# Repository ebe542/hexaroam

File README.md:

# HexaRoam

A modular six-legged robot built to explore — a learning project in Rust, robotics, and AI.

## Status

Rust firmware for Raspberry Pi Pico (RP2040) generates synchronous two-channel servo signals through one PIO state machine and DMA. Separate hardware tests exercise signal-plan switching, persistent faults, explicit restart after underflow, and aborting active DMA before recovery. The normal demo includes buffered UART logging and bounded panic output. The owner reported 169 passing unit tests and successful manual logging, panic, and recovery checks. The transactional angle-command bank and signal-plan adapter are host-tested and have passed a combined Pico angle-command signal check. A separate hardware test also verifies an exhausted DMA-abort budget and subsequent recovery. The normal firmware remains a fixed-plan demo; attached-servo operation and autonomous behavior are not yet verified. See the [firmware guide](firmware/README.md) for the verification record.

## Goals

- Build servo control, communication, kinematics, gait generation, and behavior logic step by step.
- Start with one general-purpose Raspberry Pi Pico and Rust.
- Add Pico output expansion modules when needed.
- Adapt the mechanical reference design and document each built configuration.
- Develop autonomous exploration, interaction, and later custom AI models.
- Keep ROS integration optional.

## Repository layout

| Directory | Contents |
| --- | --- |
| docs/ | Architecture, milestones, and decisions |
| hardware/mechanics/ | CAD, print files, and assembly |
| hardware/electronics/ | Wiring, power distribution, and board connections |
| hardware/bom/ | Bills of materials |
| hardware/references/ | Versioned official datasheets and reference documents |
| firmware/ | Rust firmware for Pico controllers |
| software/ | Motion, sensors, navigation, and behavior |
| simulation/ | Robot models and simulation experiments |
| tools/ | Calibration and diagnostics |
| configs/ | Geometry, joint mapping, and calibration |

Start with the [visual architecture maps](docs/architecture/README.md), [project architecture](docs/architecture.md) and [milestones](docs/milestones.md).

## Hardware reference

The initial mechanical reference is [ggldnl/Hexapod-Hardware](https://github.com/ggldnl/Hexapod-Hardware), published under CERN-OHL-W-2.0. Upstream CAD and code are not bundled in this scaffold. Record provenance and applicable licenses when importing files; see [hardware attribution](hardware/ATTRIBUTION.md).

Official Pico and RP2040 PDFs, versions, licenses, and checksums are listed in [hardware references](hardware/references/README.md).

## Development

Rust is planned for firmware, communication, kinematics, and motion control. Python is planned for AI training, analysis, and experiments. The selected board is the existing Raspberry Pi Pico with RP2040, using the Rust target `thumbv6m-none-eabi`. Rust, rust-analyzer, and the embedded target are installed on the Windows development host. The blink and adjustable PIO pulse firmware has been built and run on the Pico. The communication bus and later Linux host environment remain open.

Follow the [development setup guide](docs/development-setup.md) for Windows with Git Bash or Ubuntu. It separates confirmed setup results from pending verification.

See the [firmware guide](firmware/README.md) for build, UF2 conversion, USB transfer, and the manual verification record. Ubuntu setup is documented but has not been verified for this project.

## Licensing

Original HexaRoam software and documentation are licensed under the [MIT License](LICENSE). Third-party materials, including imported or derived hardware designs, retain their applicable licenses; see [hardware attribution](hardware/ATTRIBUTION.md).

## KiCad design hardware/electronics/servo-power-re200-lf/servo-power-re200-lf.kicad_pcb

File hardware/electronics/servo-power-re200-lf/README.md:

# One-servo protected supply on Roth RE200-LF

Revision P1, 2026-10-27. **UNBUILT placement and hand-wiring proposal.** The schematic remains [revision C](../pico-servo-system/README.md); electrical calculations and commissioning limits are in [discrete-shunt-design.md](../pico-servo-system/discrete-shunt-design.md). This layout does not establish successful protection or a current rating.

## Files and physical scope

- [Editable KiCad board](servo-power-re200-lf.kicad_pcb) and [project](servo-power-re200-lf.kicad_pro).
- [Four-page assembly guide](assembly-guide.pdf): 1 component view, 2 mirrored solder view, 3 load wiring, 4 control wiring. A4 landscape, actual size; verify the 50-mm calibration bar and real hole alignment before use.
- [Pin map](pin-map.csv), [wire list](wiring.csv), [assembly BOM](assembly-bom.csv), [layout model](layout-model.json), [check record](layout-check.json).
- SVG views provide the same geometry with hover labels. Hole IDs always refer to the component view: C01..C61, R01..R38. Solder views mirror columns horizontally only.

26 schematic components correspond to 54 physical pins, plus four existing-pad wire junctions BV/BG/BD/GS. The board has 30 footprints, 58 occupied holes and 47 insulated wire connections. U202 pin7 is intentionally unconnected. No copper tracks are provided; KiCad unrouted indications are expected. Do not export Gerbers for fabrication. Native front-side THT rings are virtual; the actual RE200-LF is single-sided, unplated, with underside pads only.

SW201 and R208 footprints represent **two-pole cable interfaces**, not the physical switch and resistor. Install the actual APEM switch separately on its bracket and the actual ARCOL HS25 2.2-ohm resistor on a suitable external heatsink. Never replace either external component with a wire short. If the optional switch is deliberately omitted, bypass its interface only with a suitably rated conductor. Keep the dump loop short and supported; the layout reserves board space, not a thermal enclosure design.

This supply is for **one servo only**. The Pico baseboard has its own Manson-to-VSYS feed; it is not powered from J202. Connect shared signal ground according to the system schematic. Three output modules reserve eighteen servo signals, but the present supply is not an eighteen-servo distribution board.

## Parts and fit

Use [the BOM](assembly-bom.csv) together with [mechanical part references](../pico-servo-system/power-layout-components.md). Four Phoenix 1715721 / MKDS 1.5/2-5.08 terminals are proposed for J201, J202 and the SW201/R208 interfaces. Equivalent terminals require their own body, drill, pin and current-rating check.

- C201, owner measured: 1000 uF/25 V, diameter 10 mm, height 20 mm, approximately 5-mm wire spacing. Gently form to 5.08 mm without stressing the seal. Pin1 positive, pin2 negative. C202/C203 are provisional 100-nF disc envelopes; match actual parts before soldering.
- F201 holder: ESKA 503.400, cover 503.310, fuse 5x20 mm. Body 22x9x13.5 mm. Native pitch 22.60 mm versus nine grid intervals = 22.86 mm. Form terminal ends gently by about 0.13 mm per side when centered; do not force the holder. Dry fit before populating. T2.5A remains a provisional fuse choice pending measured behavior.
- Widen only the occupied terminal/Q201 holes to 1.3 mm, F201/D201/D202 holes to 1.5 mm; see pin-map.csv. Existing pad diameter remains 2.2 mm (nominal annulus 0.35 mm at 1.5-mm drill). Inspect for pad damage and support heavy parts/wires mechanically. Drilling/fit is not physically verified.
- U201 is specifically ST TL431CZ: REF1, anode2, cathode3. The wide TO-92 row requires spreading leads to 2.54-mm spacing. Do not substitute another TL431 package/pinout without checking its datasheet.
- U202 is LM393 in DIP8, notch toward the upper board edge. Verify pin1 before insertion. Q201 is IRLZ44NPBF: gate1, drain2, source3. Its metal tab is drain; insulate mounting hardware/heatsink as required. Other package variants require review.
- D201 SR540 and D202 1N5822: stripe/cathode = pin1, anode = pin2. The DO-201AD envelopes and 15.24-mm formed spacing are proposed; verify actual diameters and leads.
- R201..R207 use 10.16-mm axial spacing and a 6.3x2.5-mm body envelope; select ratings from the circuit design. R208 is external and is not an axial board resistor.
- Optional M1..M4 mounting reserves are drawn, not factory holes. Check actual mounting clearances before drilling. Leave room above the 20-mm capacitor, fuse cover and screw terminals.

Local capacitor/holder footprints are derived from KiCad standard geometry or explicit manufacturer dimensions. The capacitor lead spacing and fuse terminal spacing adaptations are documented; library licensing follows the KiCad Libraries License with its electronic-design exception. The two-pin holder geometry is original project material.

## Connections and assembly order

1. Print at actual size, check the ruler, board orientation and parts against their envelopes. Dry fit the fuse holder, terminals, capacitors and MOSFET before drilling or soldering.
2. Fit low components, DIP socket if used, then taller components. Keep fuse removed, both supplies disconnected and external cables disconnected during continuity work.
3. Install the load wires from PDF page3 / CSV group `load`. Use insulated conductors sized for the measured load and dump currents, reinforced at pad nodes. A drawn line indicates endpoints, not a bare solder bridge. Do not rely on 35-um isolated pad copper or a small component lead as a power bus. BV/BG/BD are junction pads only, not extra purchased parts.
4. Install control wires from page4 / group `control`. GS provides quiet ground; join it at Q201 source as listed. R207 returns directly to that source. Keep reference/sense wiring away from dump-current wiring. Crossings are insulated passovers, never implicit junctions.
5. Connect external switch/resistor harnesses. SW201 terminal1 is fused input, terminal2 goes to D201 anode. R208 terminal1 is SERVO_VS, terminal2 is MOSFET drain. The resistor has no polarity. Check actual switch ON contact pair before attachment.
6. Inspect diode/capacitor polarity, transistor/reference pinout, resistance between rails and every listed endpoint with power off. Do not treat the check record as a substitute for these measurements.
7. Follow the existing staged [commissioning plan](../pico-servo-system/discrete-shunt-design.md) before attaching a servo. Normal rail target is 5.0-5.3 V. The dump nominal thresholds are not guaranteed maximum transient voltages. Startup, PSU interaction, clamp behavior, fuse selection and heating remain unverified.

J201: pin1 PSU positive, pin2 ground. J202: pin1 SERVO_VS, pin2 ground. Test points: TP201 rail, TP202 ground, TP203 reference, TP204 sense, TP205 gate, TP206 drain. Support cables so screw-terminal forces cannot peel pads. The external resistor may dissipate substantial power; its nameplate rating assumes appropriate cooling.

## Review boundaries

The exported board is checked against a fresh revision-C netlist: references, values, nets, pad positions, drill sizes, body envelopes, distinct occupied holes, wire-graph completeness, polarities and quiet-ground topology. These are artifact checks, not hardware tests. Wire routes are endpoint guides; actual routing, clearances, joints, transient response and thermal behavior require manual review and bench measurements. No firmware changes or firmware tests were made.

All layout files are a consistent snapshot. Moving a footprint in KiCad does not update the CSV/PDF/SVG/model automatically. Update and recheck every artifact before assembly. Do not update this board from the whole three-sheet schematic without explicitly filtering the supply sheet: the other sheets belong to separate physical boards.

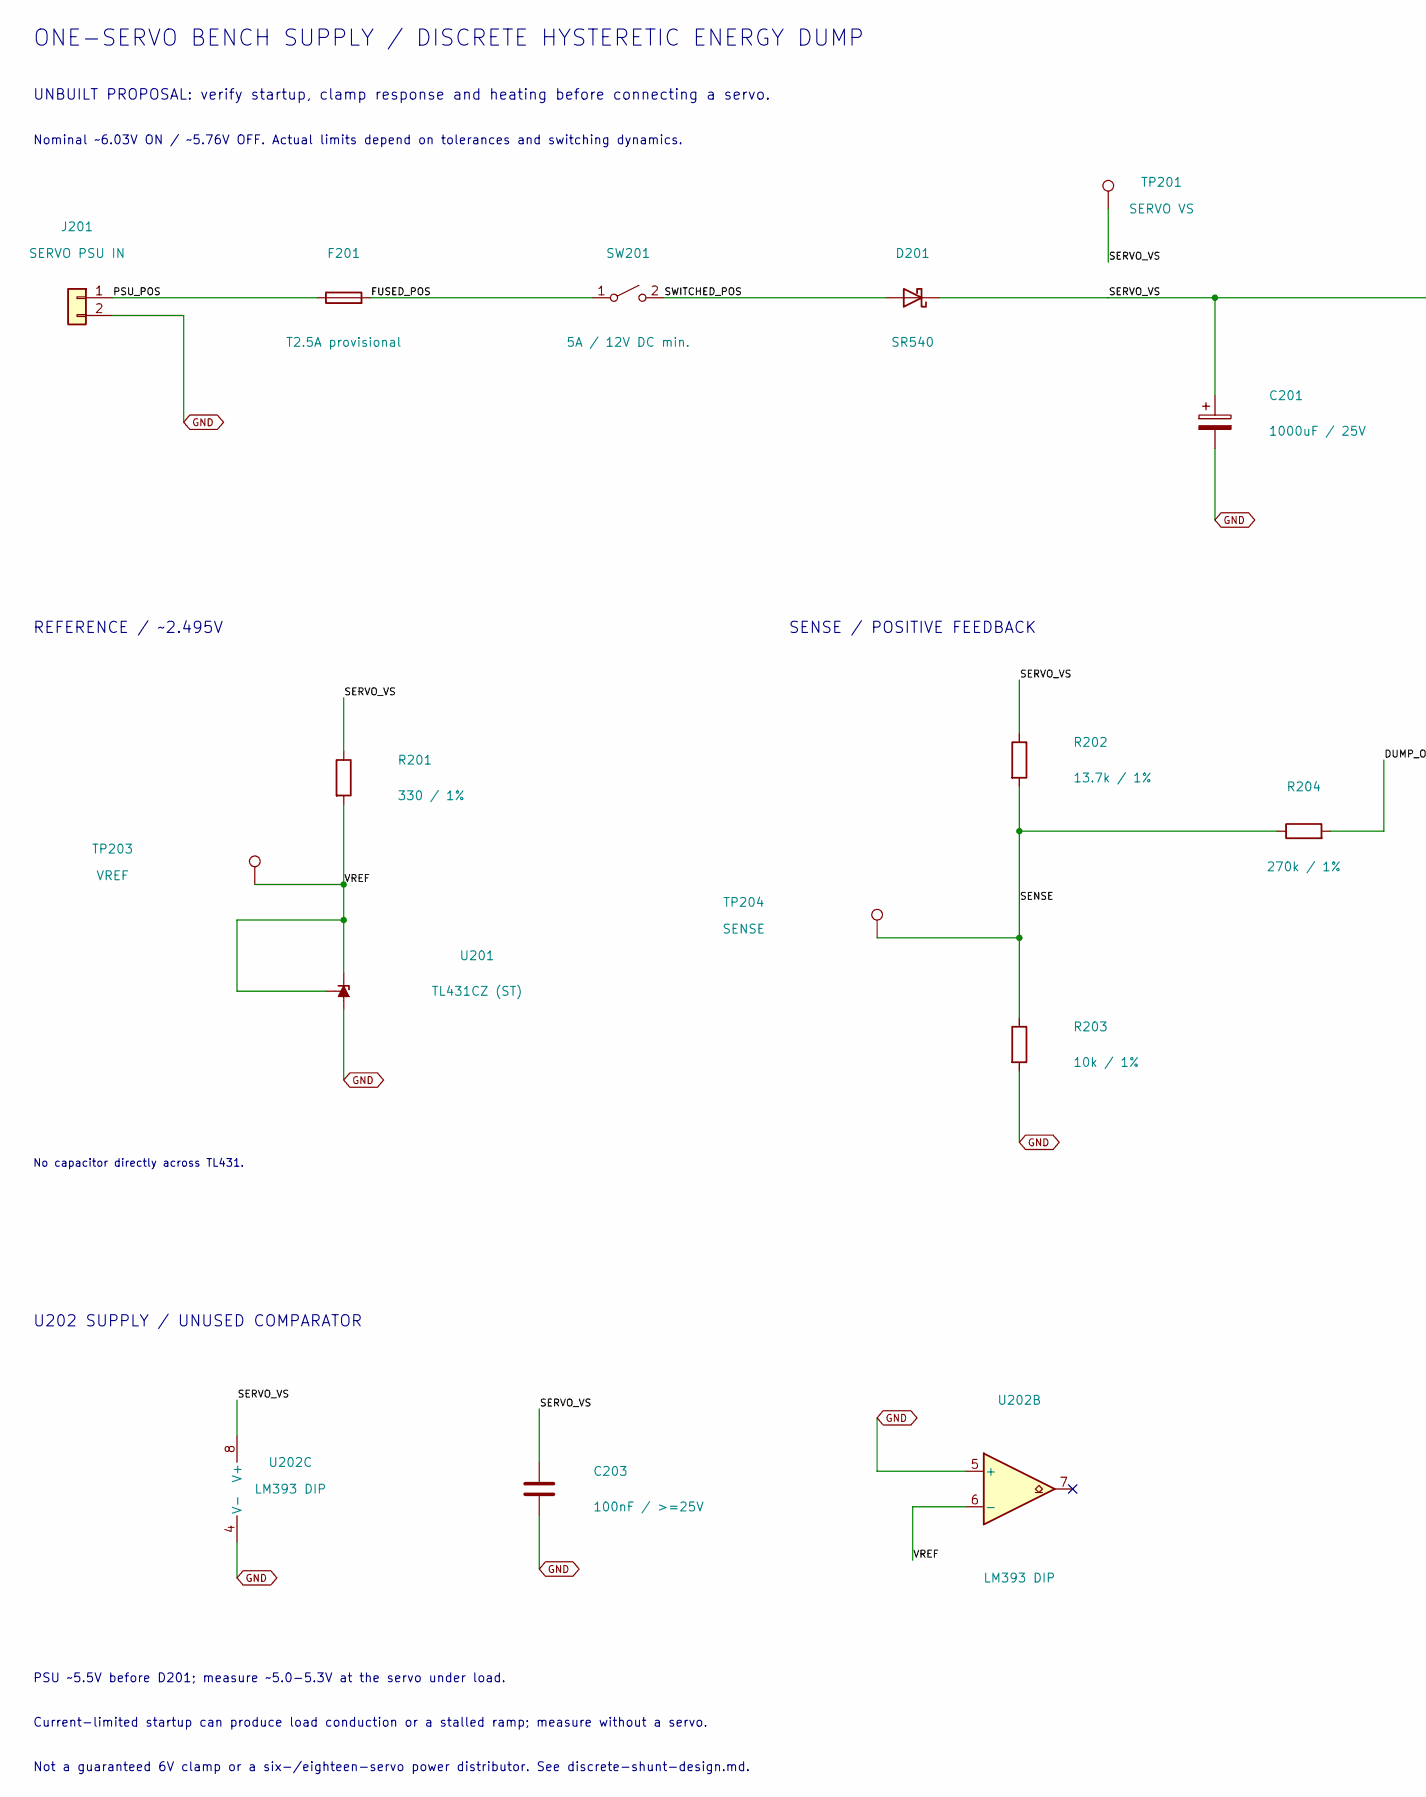
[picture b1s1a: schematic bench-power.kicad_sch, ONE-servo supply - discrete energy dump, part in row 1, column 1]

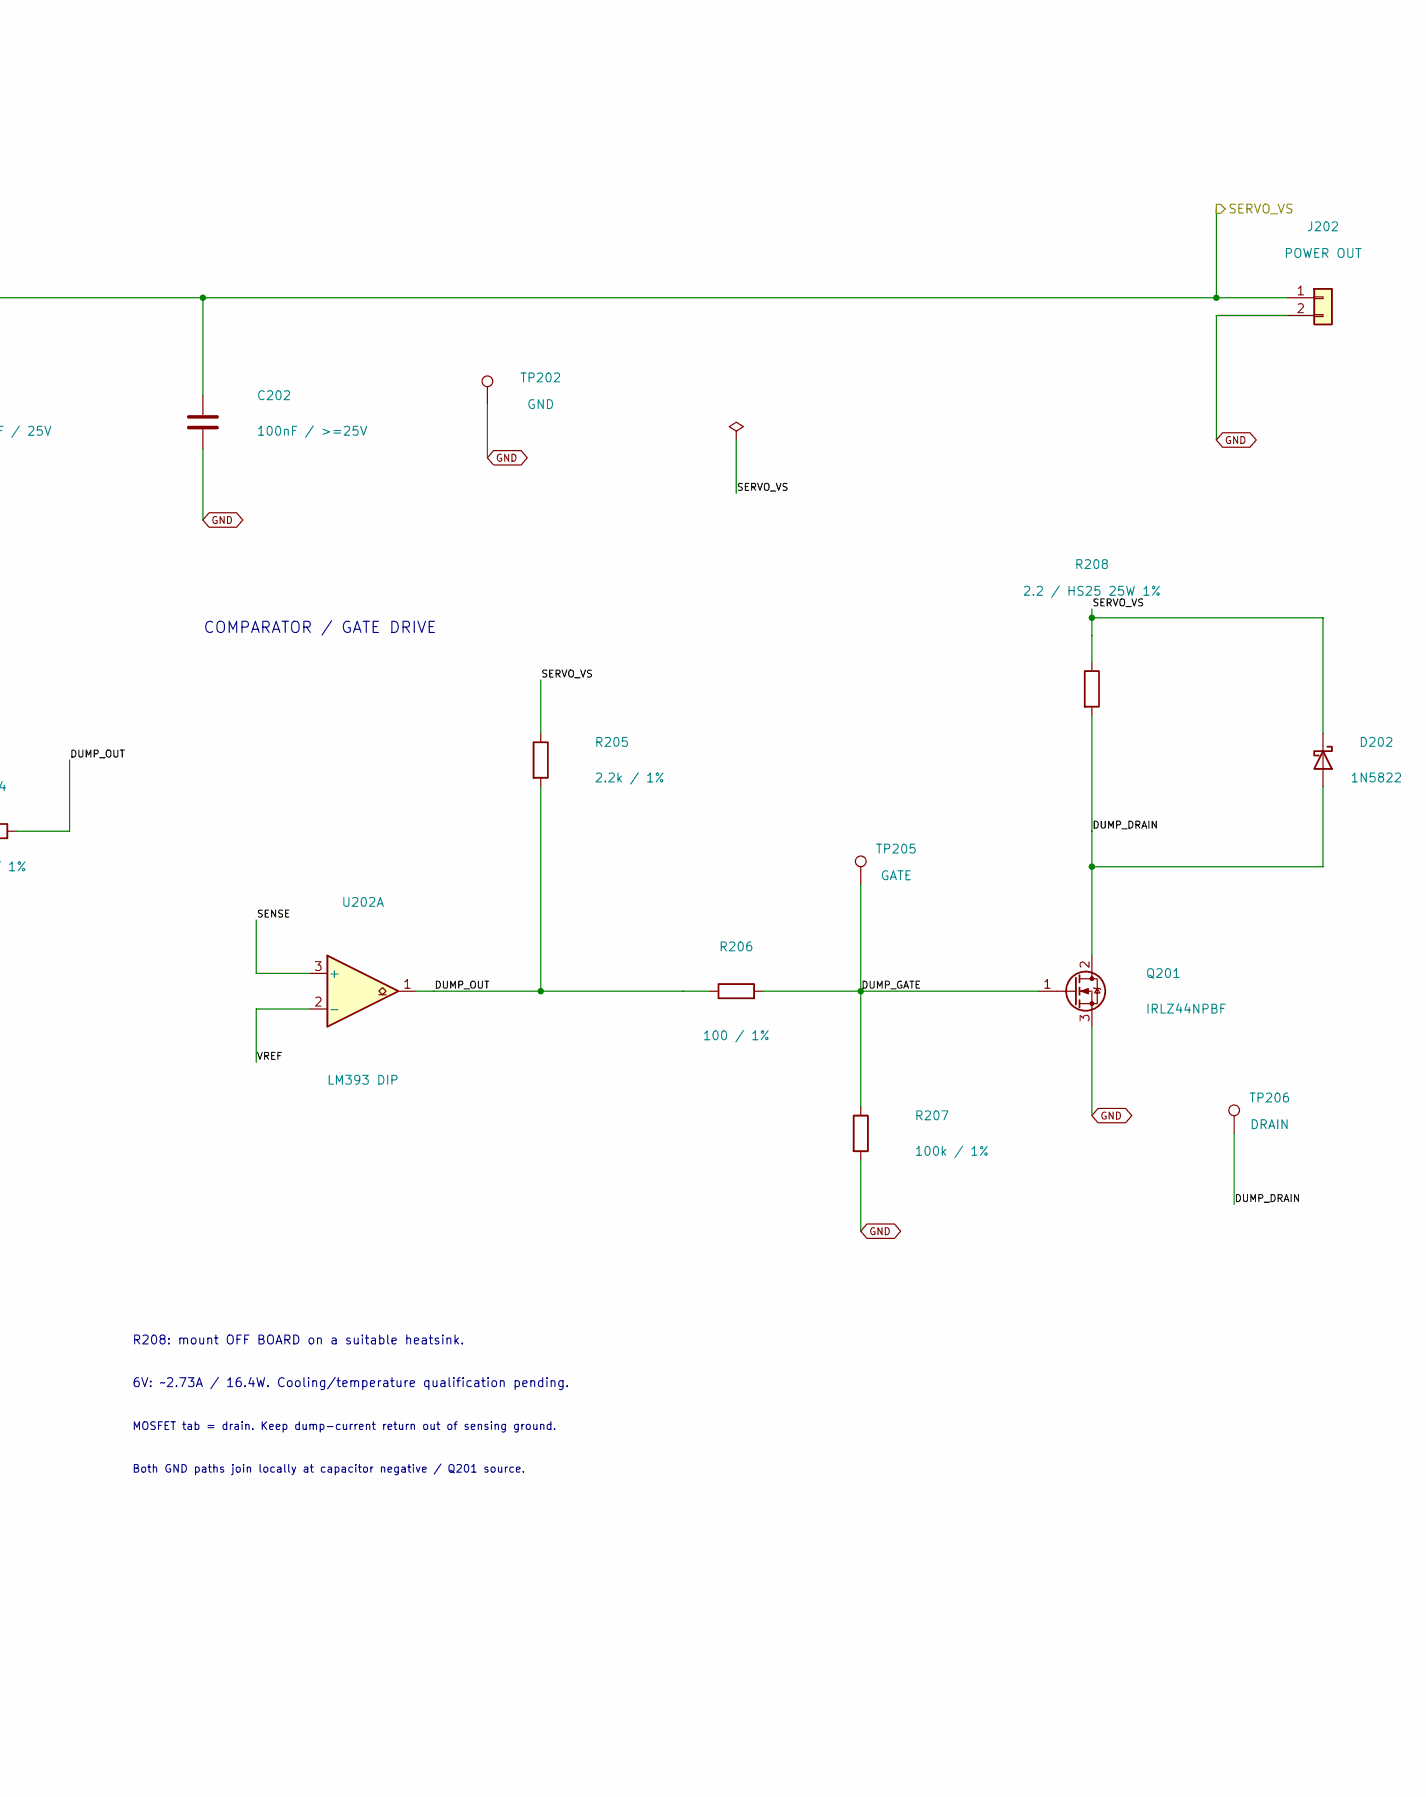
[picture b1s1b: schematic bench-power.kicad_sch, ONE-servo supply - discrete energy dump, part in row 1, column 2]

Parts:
C201: 1000uF / 25V
C202, C203: 100nF / >=25V
D201: SR540
D202: 1N5822
F201: T2.5A provisional
J201: SERVO PSU IN
J202: POWER OUT
Q201: IRLZ44NPBF; TO-220-3_Vertical
R201: 330 / 1%
R202: 13.7k / 1%
R203: 10k / 1%
R204: 270k / 1%
R205: 2.2k / 1%
R206: 100 / 1%
R207: 100k / 1%
R208: 2.2 / HS25 25W 1%
SW201: 5A / 12V DC min.
TP201: SERVO VS
TP202: GND
TP203: VREF
TP204: SENSE
TP205: GATE
TP206: DRAIN
U201: TL431CZ (ST); TO-92_Inline
U202: LM393 DIP; DIP-8_W7.62mm

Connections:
/ONE-SERVO protected supply/DUMP_DRAIN: D202.2 (A), Q201.2 (D), R208.2, TP206.1; also elsewhere on the board
/ONE-SERVO protected supply/DUMP_GATE: Q201.1 (G), R206.2, R207.1, TP205.1
/ONE-SERVO protected supply/DUMP_OUT: R204.2, R205.2, R206.1, U202.1
/ONE-SERVO protected supply/FUSED_POS: F201.2, SW201.1 (A)
/ONE-SERVO protected supply/PSU_POS: F201.1, J201.1
/ONE-SERVO protected supply/SENSE: R202.2, R203.1, R204.1, TP204.1, U202.3 (+)
/ONE-SERVO protected supply/SWITCHED_POS: D201.2 (A), SW201.2 (B)
/ONE-SERVO protected supply/VREF: R201.2, TP203.1, U201.1 (REF), U201.3 (K), U202.2 (-), U202.6 (-)
/SERVO_VS: C201.1, C202.1, C203.1, D201.1 (K), D202.1 (K), J202.1, R201.1, R202.1, R205.1, R208.1, TP201.1, U202.8 (V+); also elsewhere on the board
GND: C201.2, C202.2, C203.2, J201.2, J202.2, Q201.3 (S), R203.2, R207.2, TP202.1, U201.2 (A), U202.4 (V-), U202.5 (+); also elsewhere on the board

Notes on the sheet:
ONE-SERVO BENCH SUPPLY / DISCRETE HYSTERETIC ENERGY DUMP
UNBUILT PROPOSAL: verify startup, clamp response and heating before connecting a servo.
Nominal ~6.03V ON / ~5.76V OFF. Actual limits depend on tolerances and switching dynamics.
REFERENCE / ~2.495V
No capacitor directly across TL431.
SENSE / POSITIVE FEEDBACK
COMPARATOR / GATE DRIVE
U202 SUPPLY / UNUSED COMPARATOR
R208: mount OFF BOARD on a suitable heatsink.
6V: ~2.73A / 16.4W. Cooling/temperature qualification pending.
MOSFET tab = drain. Keep dump-current return out of sensing ground.
Both GND paths join locally at capacitor negative / Q201 source.
PSU ~5.5V before D201; measure ~5.0-5.3V at the servo under load.
Current-limited startup can produce load conduction or a stalled ramp; measure without a servo.
Not a guaranteed 6V clamp or a six-/eighteen-servo power distributor. See discrete-shunt-design.md.

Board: 2 copper layers, 30 parts (0 on the bottom side), 10 nets, no tracks yet.

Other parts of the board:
BD: /ONE-SERVO protected supply/DUMP_DRAIN; TestPoint_THTPad_D2.0mm_Drill1.0mm
BG: GND; TestPoint_THTPad_D2.0mm_Drill1.0mm
BV: /SERVO_VS; TestPoint_THTPad_D2.0mm_Drill1.0mm
GS: GND; TestPoint_THTPad_D2.0mm_Drill1.0mm

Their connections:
/ONE-SERVO protected supply/DUMP_DRAIN: BD.1; also elsewhere on the board
/SERVO_VS: BV.1; also elsewhere on the board
GND: BG.1, GS.1; also elsewhere on the board

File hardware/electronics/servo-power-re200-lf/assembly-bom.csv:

reference,quantity,value,footprint,notes
C201,1,1000uF / 25V,HexaRoam_Perfboard:CP_Radial_D10.0mm_P5.08mm_HandFormed,"Owner: D10 x H20 mm, approximate P5.00 formed to P5.08"
C202,1,100nF / >=25V,HexaRoam_Perfboard:C_Disc_D5.0mm_P2.54mm_HandFormed,
C203,1,100nF / >=25V,HexaRoam_Perfboard:C_Disc_D5.0mm_P2.54mm_HandFormed,
D201,1,SR540,Diode_THT:D_DO-201AD_P15.24mm_Horizontal,
D202,1,1N5822,Diode_THT:D_DO-201AD_P15.24mm_Horizontal,
F201,1,T2.5A provisional,HexaRoam_Perfboard:Fuseholder_ESKA503400_P22.86mm_HandFormed,ESKA 503.400 holder + 503.310 cover; provisional T2.5A 5x20 fuse; formed 22.60 -> 22.86 mm
J201,1,SERVO PSU IN,"TerminalBlock_Phoenix:TerminalBlock_Phoenix_MKDS-1,5-2-5.08_1x02_P5.08mm_Horizontal",Reference Phoenix 1715721 / MKDS 1.5/2-5.08
J202,1,POWER OUT,"TerminalBlock_Phoenix:TerminalBlock_Phoenix_MKDS-1,5-2-5.08_1x02_P5.08mm_Horizontal",Reference Phoenix 1715721 / MKDS 1.5/2-5.08
Q201,1,IRLZ44NPBF,Package_TO_SOT_THT:TO-220-3_Vertical,
R201,1,330 / 1%,Resistor_THT:R_Axial_DIN0207_L6.3mm_D2.5mm_P10.16mm_Horizontal,
R202,1,13.7k / 1%,Resistor_THT:R_Axial_DIN0207_L6.3mm_D2.5mm_P10.16mm_Horizontal,
R203,1,10k / 1%,Resistor_THT:R_Axial_DIN0207_L6.3mm_D2.5mm_P10.16mm_Horizontal,
R204,1,270k / 1%,Resistor_THT:R_Axial_DIN0207_L6.3mm_D2.5mm_P10.16mm_Horizontal,
R205,1,2.2k / 1%,Resistor_THT:R_Axial_DIN0207_L6.3mm_D2.5mm_P10.16mm_Horizontal,
R206,1,100 / 1%,Resistor_THT:R_Axial_DIN0207_L6.3mm_D2.5mm_P10.16mm_Horizontal,
R207,1,100k / 1%,Resistor_THT:R_Axial_DIN0207_L6.3mm_D2.5mm_P10.16mm_Horizontal,
R208,1,2.2 / HS25 25W 1%,"TerminalBlock_Phoenix:TerminalBlock_Phoenix_MKDS-1,5-2-5.08_1x02_P5.08mm_Horizontal",Actual part off-board: ARCOL HS25 2.2 ohm with heatsink; footprint is cable terminal only
SW201,1,5A / 12V DC min.,"TerminalBlock_Phoenix:TerminalBlock_Phoenix_MKDS-1,5-2-5.08_1x02_P5.08mm_Horizontal",Actual part off-board: APEM 3631NF/2; footprint is cable terminal only
TP201,1,SERVO VS,TestPoint:TestPoint_THTPad_D2.0mm_Drill1.0mm,
TP202,1,GND,TestPoint:TestPoint_THTPad_D2.0mm_Drill1.0mm,
TP203,1,VREF,TestPoint:TestPoint_THTPad_D2.0mm_Drill1.0mm,
TP204,1,SENSE,TestPoint:TestPoint_THTPad_D2.0mm_Drill1.0mm,
TP205,1,GATE,TestPoint:TestPoint_THTPad_D2.0mm_Drill1.0mm,
TP206,1,DRAIN,TestPoint:TestPoint_THTPad_D2.0mm_Drill1.0mm,
U201,1,TL431CZ (ST),Package_TO_SOT_THT:TO-92_Inline_Wide,
U202,1,LM393 DIP,Package_DIP:DIP-8_W7.62mm,
MECH1,1,Roth RE200-LF 100x160 mm,,Single-sided 38x61 grid
MECH2,2,Phoenix 1715721 2-pole terminal,,Additional SW201/R208 cable interfaces; actual external parts already listed separately
MECH3,1,DIP8 socket optional,,Check actual height/body
MECH4,1,"Insulated wire, harness terminals, mounting support",,Size for measured currents; not a fixed kit
MECH5,1,External heatsink and insulated mounting as needed,,R208 mandatory cooling; Q201 heating requires verification

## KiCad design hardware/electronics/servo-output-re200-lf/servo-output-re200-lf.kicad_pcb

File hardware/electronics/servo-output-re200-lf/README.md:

# Six-channel servo-output module on RE200-LF

P1, 2026-10-27: unbuilt hand-wiring layout for page 2 of the [revision C system schematic](../pico-servo-system/README.md). All six channels are placed; only channel 0 is initially populated and connected. The present power system remains a ONE-servo proposal.

## Review files

- [Editable KiCad board](servo-output-re200-lf.kicad_pcb), [project](servo-output-re200-lf.kicad_pro).
- [Assembly PDF, eleven pages at 1:1](assembly-guide.pdf). Pages 1-4 cover the first assembly; pages 5-11 are future/DNP reservations.
- [Component view](placement-top.svg), [mirrored solder view](placement-bottom.svg).
- First wiring: [power/ground](wiring-initial-power.svg), [channel 0](wiring-channel-0.svg), and the [32-wire CSV](wiring-initial.csv).
- [Complete 142-wire CSV](wiring.csv), [pin map](pin-map.csv), [assembly BOM](assembly-bom.csv).
- [Layout model](layout-model.json), [connection/geometry record](layout-check.json).

The extra twelve BVx/BGx locations are existing solder pads used as wire junctions, not twelve purchased components. The complete layout has 71 schematic components, 168 source pins and these twelve additional wire-anchor pads. Native KiCad DNP marks include the 55 reserved channel parts and ten reserved wire anchors. Initial assembly has 16 electronic/connector parts, BV0/BG0 and 32 wire connections.

## Board coordinates and printing

Use Roth RE200-LF, single-sided FR4, 1.5-mm thickness, 61 columns by 38 rows, 2.54-mm pitch and 1.0-mm existing holes. The nominal board size is 100x160 mm; the manufacturer drawing gives 160.15x100.20 mm. Our coordinate origin is the drawing's first hole at x=3.89, y=3.07 mm, viewed from the component side with copper underneath:

```text
C01-R01 = top-left hole
x = 3.89 + (column - 1) * 2.54 mm
y = 3.07 + (row - 1) * 2.54 mm
```

The solder view is mirrored horizontally: column 61 at left, column 1 at right, row 1 still at top. Hole IDs refer to the same physical holes in every view, independent of manufacturer printing. Never mirror the solder-side PDF a second time.

Print at Actual size / 100%, without Fit/Shrink. Check the 50-mm line and three separated existing holes against the real board before assembly. Dimensions and connector bodies still need a dry fit; do not treat the drawings as a production PCB or drill every existing hole.

## First assembly and connector polarity

Fit common J101, J102, C100, TP101/TP102 and channel 0: Q101/Q102, R101..R107, C101 and J110. Leave all other channel parts and BV1..BV5/BG1..BG5 unpopulated/unwired. The optional extension requires a fresh power-system review.

| Item | Assignment / physical location |
| --- | --- |
| J101 | Keyed 2x6 IDC input, pin 1 C07-R04; odd pins S0..S5, all even pins GND |
| IDC key notch | Toward smaller column numbers in component view; opposite side in mirrored solder view |
| J102 | Separate servo power: pin 1 positive at C20-R04, pin 2 GND at C18-R04 |
| J110..J115 | Each: pin 1 signal, pin 2 positive, pin 3 GND |
| C100 | Positive pin 1 C26-R07, negative pin 2 C28-R07 |
| TP101 | Buffered channel-0 signal, C22-R22 |
| TP102 | GND, C14-R04 |
| BV0 / BG0 | Dedicated existing-pad junctions: positive C05-R22 / ground C07-R22 |

Servo headers are horizontal three-pin rows. In component view the pins run 1,2,3 toward larger column numbers; the solder view reverses their visual order. Verify the servo plug and the actual wire colors before insertion. Confirm the molded pin-1/key marks on the actual IDC parts, and test a straight-through cable end to end with power off.

The input interface matches all three Pico ports. On port A local S0..S5 correspond to GP0..GP5, on B to GP6..GP11, on C to GP12..GP17. This one module layout is reusable; channels do not contain leg/joint assignments or a second controller.

## Measured and assumed component geometry

The owner measured the existing 470-uF/35-V C100 as diameter 10 mm, height 20 mm, 5.00-mm lead pitch. This layout uses adjacent-grid spacing 5.08 mm; gently form the flexible leads by the total 0.08-mm difference without pushing sideways on the capacitor seal. Observe polarity. Reserve clearance above its 20-mm body.

100-nF capacitor C101 uses a compact radial/disc reference envelope approximately 5mm wide by 2.5mm thick. Its reference 2.50-mm lead pitch is gently formed to 2.54 mm in the local footprint. Verify actual purchased capacitors fit; do not replace them with larger bodies without checking the model.

The BC547B footprint uses a wide inline TO-92 lead row, 2.54-mm spacing. The selected purchasing reference is Diotec BC547B (Reichelt BC 547B DIO); its checked manufacturer drawing defines pins 1/2/3 as collector/base/emitter. The flat-body edge is drawn in the placement view. Identify the manufacturer/package of the supplied transistors and check its pinout before soldering; do not guess from a different transistor or view direction. Spread leads gently away from the body as needed, and keep some lead length for forming. The modeled TO-92 body reserve is 5.2x5.2 mm.

Resistors use a DIN0207 reference body 6.3x2.5mm with 10.16-mm hole spacing; metal-film parts >=0.25W with bodies fitting that envelope are suitable references. The schematic values remain unchanged: 4.7k input/interstage, 1k collector pull-ups, 100k pull-downs, 180-ohm output series resistor. Dry-fit the actual parts.

J102 uses the same Phoenix MKDS 1,5/2-5,08 reference style as the Pico supply terminal, part 1715721. Enlarge ONLY C20-R04 and C18-R04 from 1.0 to 1.3 mm if using that part. Inspect pad rings and support the body during screw tightening. A terminal's headline current rating is not a rating of this entire handmade board.

Optional M3 reserves are C03-R03, C59-R03, C03-R36 and C59-R36. The drawn 3.2-mm holes do not exist yet. Leave the marked 4-mm-radius areas and nearby pads clear; decide real spacers/washers before drilling and inspect for damaged copper.

## Power wiring and initial-versus-future wires

The wire tables distinguish logic connections from role=load connections (marked * in the PDF). Load wires directly connect J102, C100, the BV/BG junctions and servo power/return pins. Motor supply current must not pass through resistor or transistor leads, or return through the IDC cable. Choose reinforced conductors appropriate for measured single-servo current and provide strain relief. Join wire ends directly at each solder junction rather than relying on a narrow solder bridge or forcing several wires into a hole.

BVx/BGx are already existing unused solder eyes; no extra header is required. A continuous suitably reinforced conductor with soldered branch taps can implement successive load-wire segments. Protect the insulated main conductor from component tails. The drawings show which endpoints connect, not a fully qualified physical wire route. There are no electrical connections at crossing lines. Keep exposed ends short and separated; crossings require intact insulation. Up to three wire ends are allocated to any one junction in the complete proposed tree.

The initial 32-wire graph is independently connected and uses ONLY fitted parts and BV0/BG0. It does not require any DNP resistor/servo pad as a feed-through. The full graph has 142 wires; its other 110 entries are future reservations. In particular, do not add all motor-power branches and then connect six servos to the present supply. Six-channel supply/return conductors, distribution, fuse, transient absorption and connector selection require current/thermal measurements and sizing first.

The buffer pulls signal high toward SERVO_VS. This remains the approximately 5-V bench proposal. Increasing motor supply voltage requires checking permissible signal voltage as well. The servo input thresholds and real loaded edge/pulse behavior are not established by the layout. Use the scope at the actual servo connector before attaching a motor.

## Manual build/check sequence

1. Check the 1:1 print, actual connector bodies, polarity and capacitor fit. Decide the terminal/mounting drilling first. Fit only common parts and channel 0; fit no servo yet.
2. Work through wiring-initial.csv or PDF pages 3/4, marking each completed wire. Keep reinforced power paths separate from logic/signal wiring and mechanically supported.
3. With power, Pico and servo disconnected, verify all listed endpoint continuities and inspect solder joints. Check there is no unintended positive-to-ground short, no adjacent IDC pin bridge and no accidental connection to DNP pads. Account for C100 charging during resistance measurements.
4. Verify the IDC cable pin-for-pin. Establish common ground with the two supplies/USB/UART/scope before power. First power the module from an appropriately limited low-voltage source with servo unplugged; confirm polarity and rail voltage.
5. Feed the established unloaded Pico PWM into S0. Measure J110 pin 1 relative to pin 3: output amplitude, pulse width, edge shape and low behavior. Confirm channels 1..5 are still unpopulated. Actual servo commissioning waits for the separately verified power protection.

These are owner-performed checks. No firmware tests or hardware experiments were run as part of drawing this layout.

## KiCad and verification boundaries

Open this controller-independent module board directly or through its local project. It derives from only the system's output sheet; do not blindly import the complete three-sheet schematic into this one physical board. The schematic itself was not changed.

F.Fab/F.SilkS show component references; Dwgs.User shows the existing grid and optional mounting reserves; Cmts.User shows insulated-wire endpoint guides. There are no copper tracks. Native unconnected/DNP indicators are expected and do not constitute a passed production PCB DRC. Standard native THT pad front rings are virtual: the actual RE200-LF is single-sided and not plated through. Do not send this layout as fabrication/Gerber data.

The local capacitor footprints adapt standard-library pad pitch to hand-formed leads on the existing grid. The PDF, SVG, CSV and KiCad files form one checked snapshot; moving a footprint in KiCad does not update the other files automatically. Reconcile them before building a changed revision. layout-check.json records hashes of the checked artifacts.

Independent checks reload the native KiCad board, compare all 168 source pins and DNP states to the freshly exported schematic, verify unique grid positions and separated body envelopes, and check both initial/full wire graphs. Additional checks ensure dedicated load-only paths from each servo power/ground pin to J102 without IDC or small-component leads. These establish drawing consistency, not current capacity, motor safety, timing accuracy or physical fit.

## Sources and licensing

- [System schematic and values](../pico-servo-system/README.md), output sheet revision C.
- [Roth RE200-LF drawing](https://www.roth-elektronik.com/pdf/en_RE200-LF.pdf); unmodified local copy/source hash under ignored local-data/perfboard/.
- [Diotec BC546..BC549 datasheet](https://diotec.com/request/datasheet/bc546.pdf), version 2026-03-30: pin1 collector, pin2 base, pin3 emitter; body and lead forms reviewed. Unmodified local PDF/source hash under ignored local-data/servo-output/. [Reichelt BC 547B DIO](https://www.reichelt.de/de/de/shop/produkt/bipolartransistor_npn_45v_0_1a_0_5w_to-92-219082) is the purchasing reference. A differently numbered manufacturer variant requires rechecking the package orientation; the type name alone is insufficient.
- C100 geometry is the owner's measured information from 2026-10-27.
- [Reference terminal at Reichelt](https://www.reichelt.com/de/en/shop/product/pcb_terminal_2-pin_spacing_5_08_mm_0_14_-_1_5_mm_-440491), part 1715721; [manufacturer dimensions](https://www.phoenixcontact.com/gb/products/1715721/pdf).
- Standard/derived footprint geometry comes from installed KiCad 10.0 libraries under the [KiCad Libraries License and design exception](https://gitlab.com/kicad/libraries/kicad-footprints/-/blob/master/LICENSE.md). Project placement/wire data and explanations are under the repository MIT license; upstream footprint and datasheet rights remain separate.

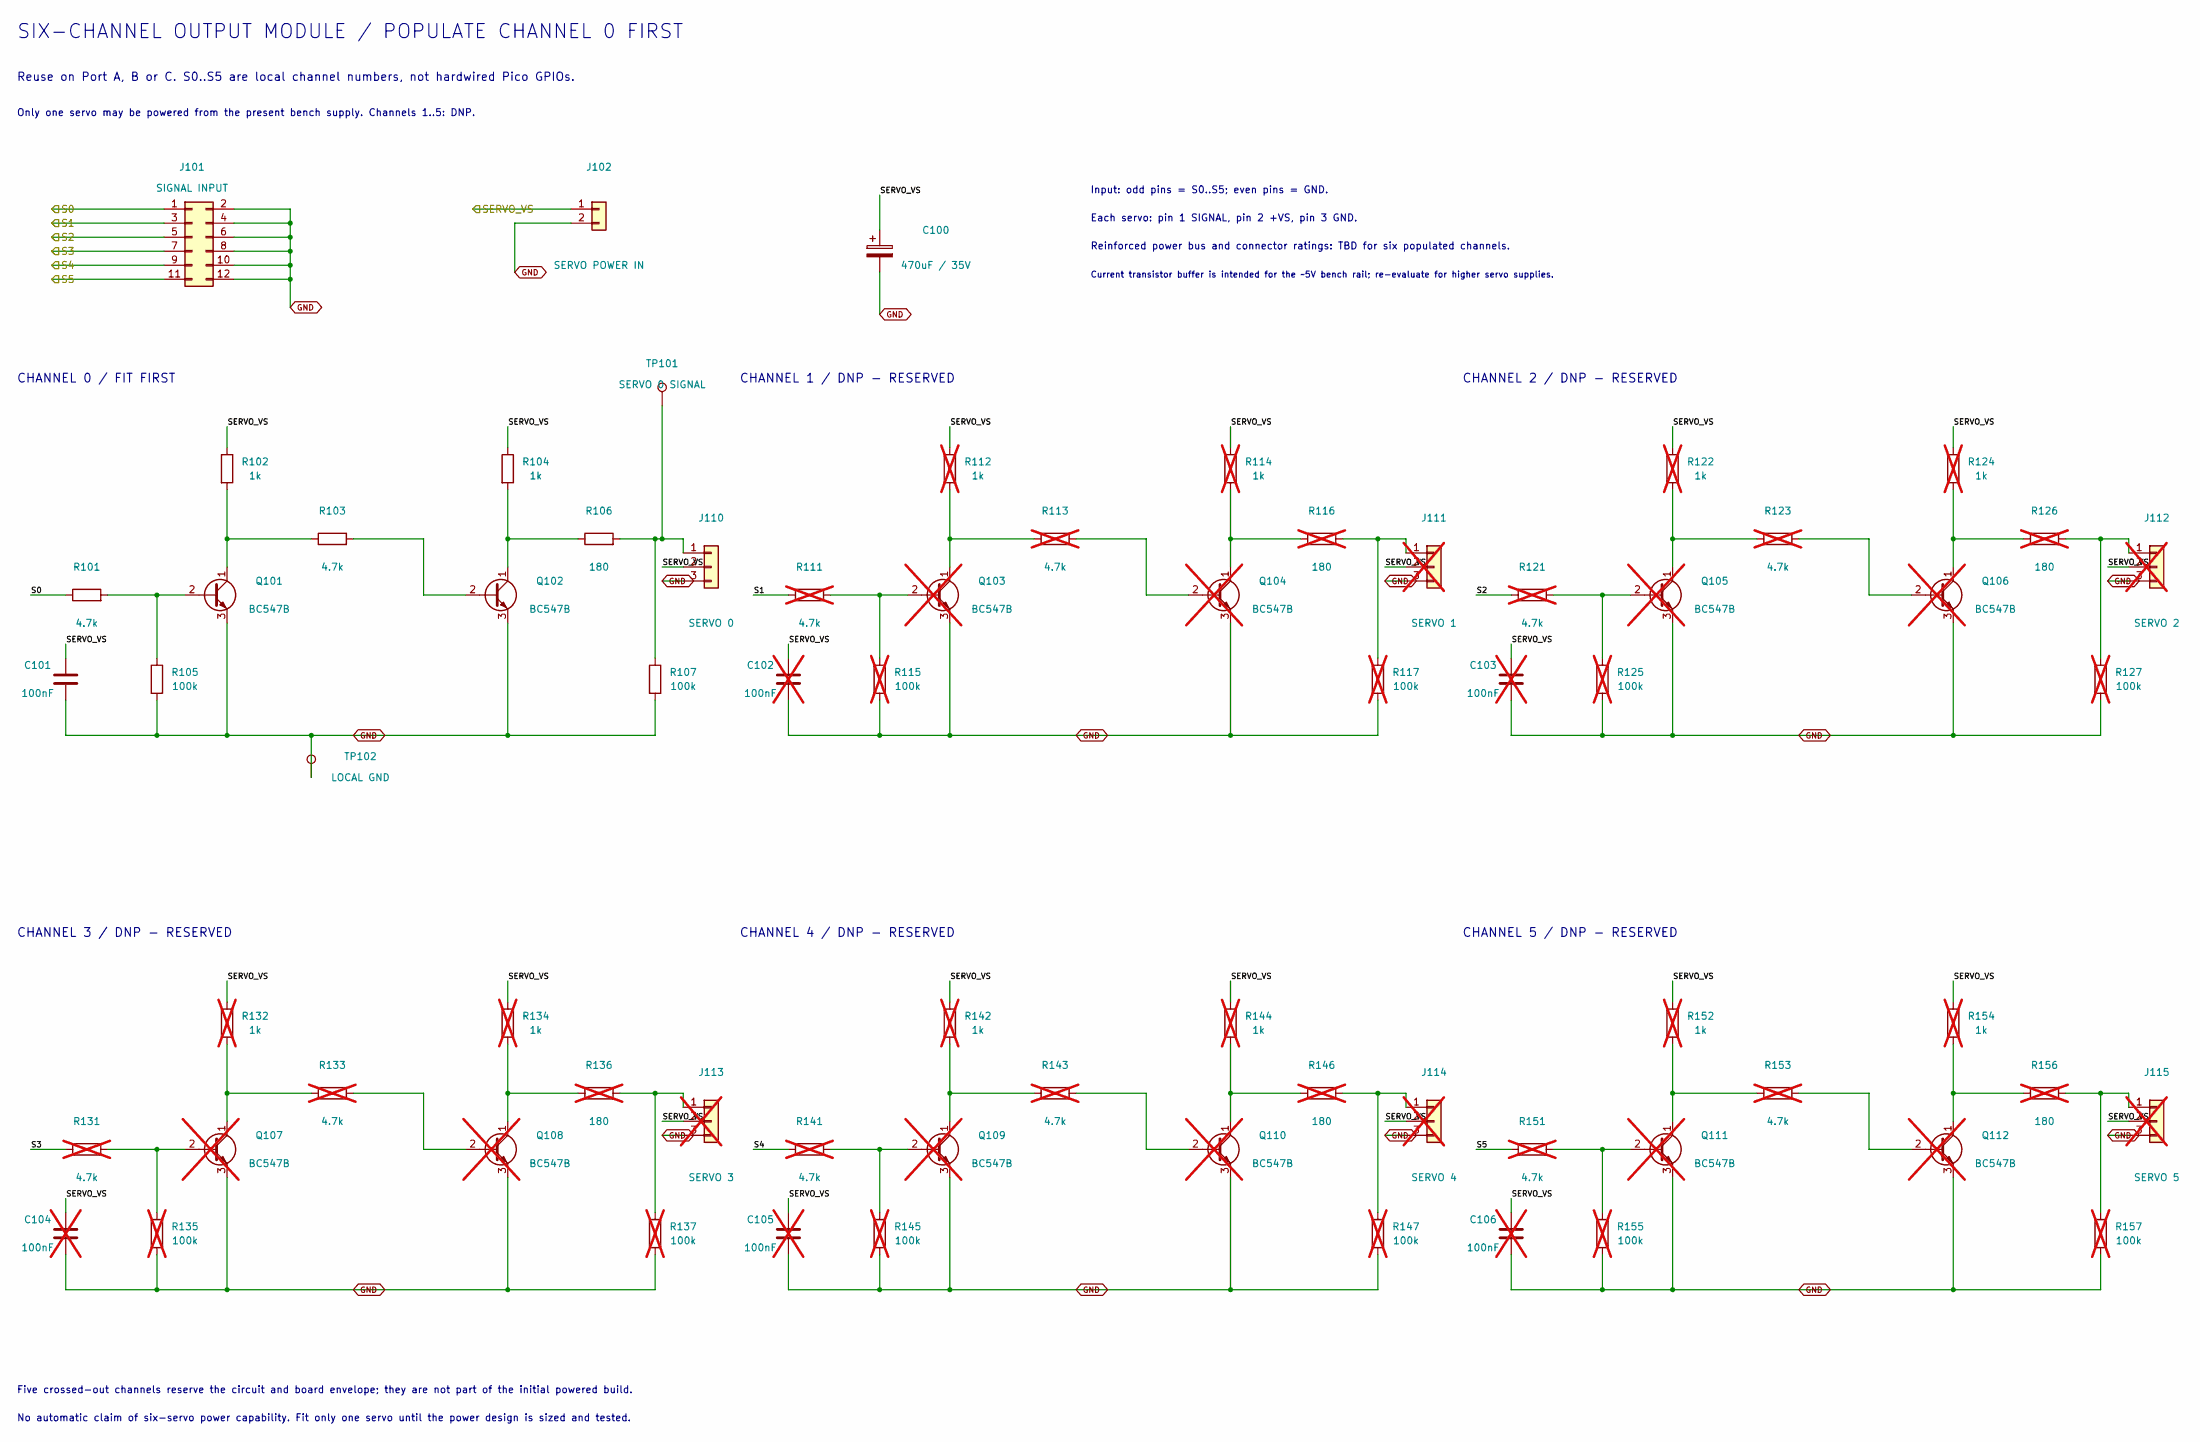
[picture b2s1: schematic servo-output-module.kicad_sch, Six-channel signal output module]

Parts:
C100: 470uF / 35V
C101: 100nF
C102, C103, C104, C105, C106: 100nF; not fitted
J101: SIGNAL INPUT; IDC-Header_2x06_P2.54mm_Vertical
J102: SERVO POWER IN
J110: SERVO 0
J111: SERVO 1; not fitted
J112: SERVO 2; not fitted
J113: SERVO 3; not fitted
J114: SERVO 4; not fitted
J115: SERVO 5; not fitted
Q101, Q102: BC547B; TO-92_Inline
Q103, Q104, Q105, Q106, Q107, Q108, Q109, Q110, Q111, Q112: BC547B; TO-92_Inline; not fitted
R101, R103: 4.7k
R102, R104: 1k
R105, R107: 100k
R106: 180
R111, R113, R121, R123, R131, R133, R141, R143, R151, R153: 4.7k; not fitted
R112, R114, R122, R124, R132, R134, R142, R144, R152, R154: 1k; not fitted
R115, R117, R125, R127, R135, R137, R145, R147, R155, R157: 100k; not fitted
R116, R126, R136, R146, R156: 180; not fitted
TP101: SERVO 0 SIGNAL
TP102: LOCAL GND

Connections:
/SERVO0_3V3: J101.1, R101.1
/SERVO1_3V3: J101.3, R111.1
/SERVO2_3V3: J101.5, R121.1
/SERVO3_3V3: J101.7, R131.1
/SERVO4_3V3: J101.9, R141.1
/SERVO5_3V3: J101.11, R151.1
/SERVO_VS: C100.1, C101.1, C102.1, C103.1, C104.1, C105.1, C106.1, J102.1, J110.2, J111.2, J112.2, J113.2, J114.2, J115.2, R102.1, R104.1, R112.1, R114.1, R122.1, R124.1, R132.1, R134.1, R142.1, R144.1, R152.1, R154.1; also elsewhere on the board
GND: C100.2, C101.2, C102.2, C103.2, C104.2, C105.2, C106.2, J101.2, J101.4, J101.6, J101.8, J101.10, J101.12, J102.2, J110.3, J111.3, J112.3, J113.3, J114.3, J115.3, Q101.3 (E), Q102.3 (E), Q103.3 (E), Q104.3 (E), Q105.3 (E), Q106.3 (E), Q107.3 (E), Q108.3 (E), Q109.3 (E), Q110.3 (E), Q111.3 (E), Q112.3 (E), R105.2, R107.2, R115.2, R117.2, R125.2, R127.2, R135.2, R137.2, R145.2, R147.2, R155.2, R157.2, TP102.1; also elsewhere on the board
unnamed: J110.1, R106.2, R107.1, TP101.1
unnamed: J111.1, R116.2, R117.1
unnamed: J112.1, R126.2, R127.1
unnamed: J113.1, R136.2, R137.1
unnamed: J114.1, R146.2, R147.1
unnamed: J115.1, R156.2, R157.1
unnamed: Q101.2 (B), R101.2, R105.1
unnamed: Q101.1 (C), R102.2, R103.1
unnamed: Q102.2 (B), R103.2
unnamed: Q102.1 (C), R104.2, R106.1
unnamed: Q103.2 (B), R111.2, R115.1
unnamed: Q103.1 (C), R112.2, R113.1
unnamed: Q104.2 (B), R113.2
unnamed: Q104.1 (C), R114.2, R116.1
unnamed: Q105.2 (B), R121.2, R125.1
unnamed: Q105.1 (C), R122.2, R123.1
unnamed: Q106.2 (B), R123.2
unnamed: Q106.1 (C), R124.2, R126.1
unnamed: Q107.2 (B), R131.2, R135.1
unnamed: Q107.1 (C), R132.2, R133.1
unnamed: Q108.2 (B), R133.2
unnamed: Q108.1 (C), R134.2, R136.1
unnamed: Q109.2 (B), R141.2, R145.1
unnamed: Q109.1 (C), R142.2, R143.1
unnamed: Q110.2 (B), R143.2
unnamed: Q110.1 (C), R144.2, R146.1
unnamed: Q111.2 (B), R151.2, R155.1
unnamed: Q111.1 (C), R152.2, R153.1
unnamed: Q112.2 (B), R153.2
unnamed: Q112.1 (C), R154.2, R156.1

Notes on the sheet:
SIX-CHANNEL OUTPUT MODULE / POPULATE CHANNEL 0 FIRST
Reuse on Port A, B or C. S0..S5 are local channel numbers, not hardwired Pico GPIOs.
Only one servo may be powered from the present bench supply. Channels 1..5: DNP.
Input: odd pins = S0..S5; even pins = GND.
Each servo: pin 1 SIGNAL, pin 2 +VS, pin 3 GND.
Reinforced power bus and connector ratings: TBD for six populated channels.
Current transistor buffer is intended for the ~5V bench rail; re-evaluate for higher servo supplies.
CHANNEL 0 / FIT FIRST
CHANNEL 1 / DNP - RESERVED
CHANNEL 2 / DNP - RESERVED
CHANNEL 3 / DNP - RESERVED
CHANNEL 4 / DNP - RESERVED
CHANNEL 5 / DNP - RESERVED
Five crossed-out channels reserve the circuit and board envelope; they are not part of the initial powered build.
No automatic claim of six-servo power capability. Fit only one servo until the power design is sized and tested.
